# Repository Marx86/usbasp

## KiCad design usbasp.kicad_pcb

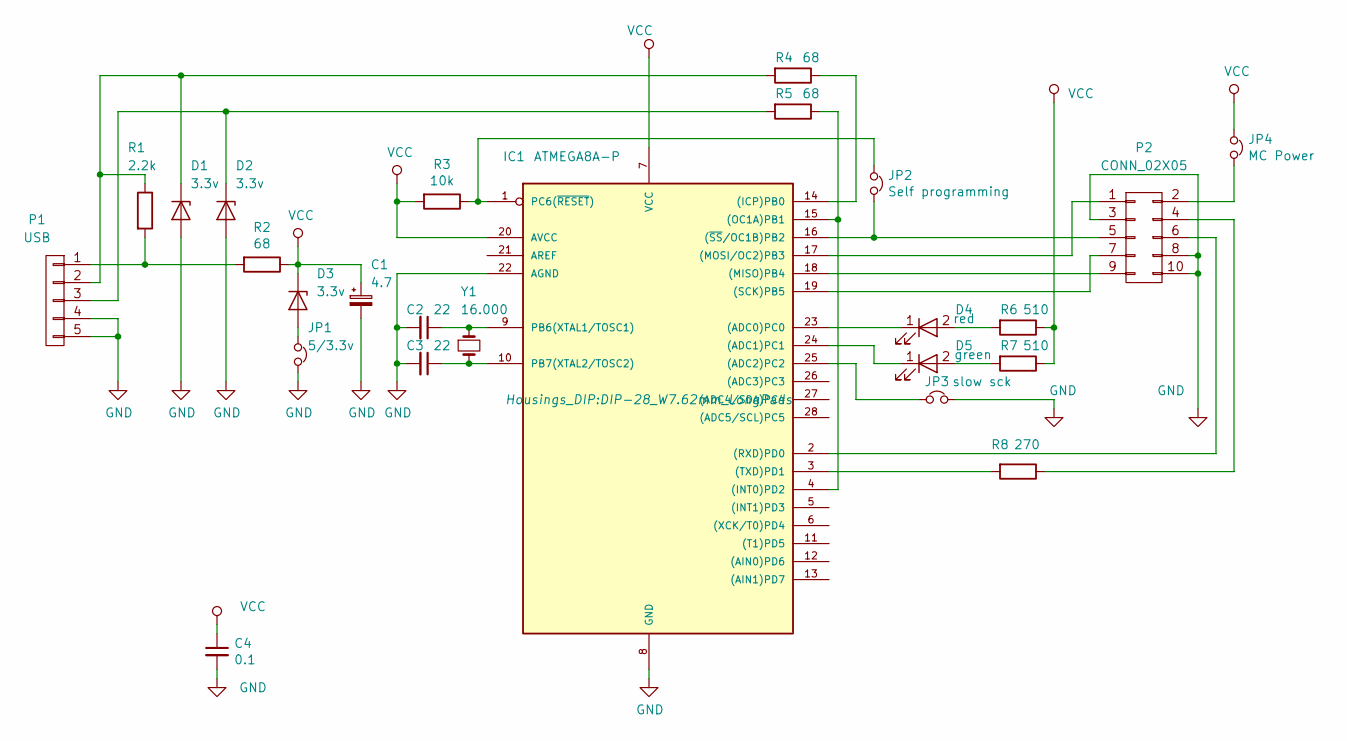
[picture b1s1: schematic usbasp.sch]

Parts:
C1: 4.7; CP_Radial_D5.0mm_P2.50mm
C2, C3: 22; C_1206
C4: 0.1; C_1206
D1, D2, D3: 3.3v; D_MiniMELF
D4: red; LED-3MM
D5: green; LED-3MM
IC1: ATMEGA8A-P; DIP-28_W7.62mm_LongPads
JP1: 5/3.3v; Pin_Header_Straight_1x02_Pitch2.54mm
JP2: Self programming; Pin_Header_Straight_1x02_Pitch2.54mm
JP3: slow sck; Pin_Header_Straight_1x02_Pitch2.54mm
JP4: MC Power; Pin_Header_Straight_1x02_Pitch2.54mm
P1: USB; USB_B
P2: CONN_02X05; Pin_Header_Straight_2x05_Pitch2.54mm
R1: 2.2k; R_1206
R2, R4, R5: 68; R_1206
R3: 10k; R_1206
R6, R7: 510; R_1206
R8: 270; R_1206
Y1: 16.000; Crystal_HC50-U_Vertical

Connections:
GND: C1.2, C2.2, C3.2, C4.2, D1.2 (A), D2.2 (A), IC1.8 (GND), IC1.22 (AGND), JP1.2, JP3.2, P1.4, P1.5, P2.3, P2.8, P2.10
unnamed: C2.1, IC1.9 (PB6(XTAL1/TOSC1)), Y1.1
unnamed: C3.1, IC1.10 (PB7(XTAL2/TOSC2)), Y1.2
unnamed: D1.1 (K), P1.2, R1.1, R4.2
unnamed: D2.1 (K), P1.3, R5.2
unnamed: D3.2 (A), JP1.1
unnamed: D4.1 (K), IC1.23 ((ADC0)PC0)
unnamed: D4.2 (A), R6.2
unnamed: D5.1 (K), IC1.24 ((ADC1)PC1)
unnamed: D5.2 (A), R7.2
unnamed: IC1.1 (PC6(~RESET~)), JP2.1, R3.1
unnamed: IC1.2 ((RXD)PD0), P2.6
unnamed: IC1.3 ((TXD)PD1), R8.2
unnamed: IC1.14 ((ICP)PB0), R4.1
unnamed: IC1.4 ((INT0)PD2), IC1.15 ((OC1A)PB1), R5.1
unnamed: IC1.16 ((~SS~/OC1B)PB2), JP2.2, P2.5
unnamed: IC1.17 ((MOSI/OC2)PB3), P2.1
unnamed: IC1.18 ((MISO)PB4), P2.9
unnamed: IC1.19 ((SCK)PB5), P2.7
unnamed: IC1.25 ((ADC2)PC2), JP3.1
unnamed: JP4.2, P2.2
unnamed: P1.1, R1.2, R2.2
unnamed: P2.4, R8.1
VCC: C1.1, C4.1, D3.1 (K), IC1.7 (VCC), IC1.20 (AVCC), JP4.1, R2.1, R3.2, R6.1, R7.1

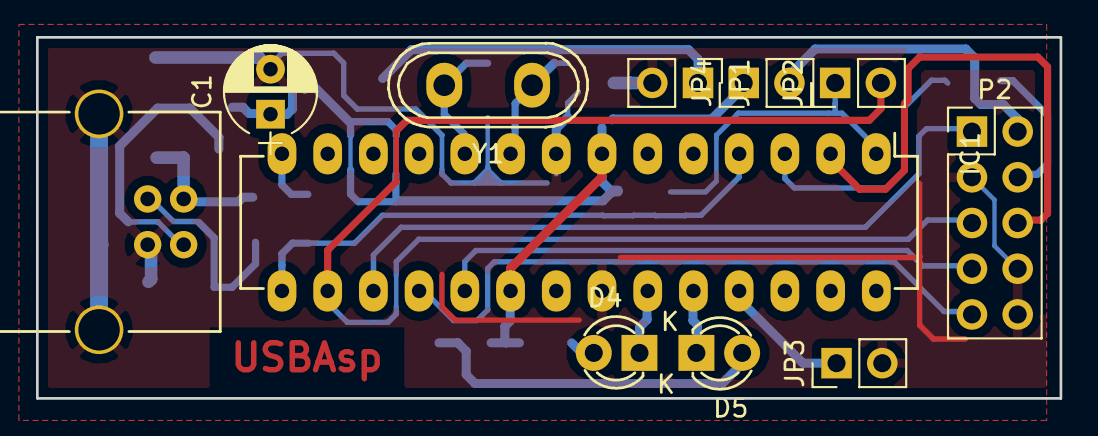
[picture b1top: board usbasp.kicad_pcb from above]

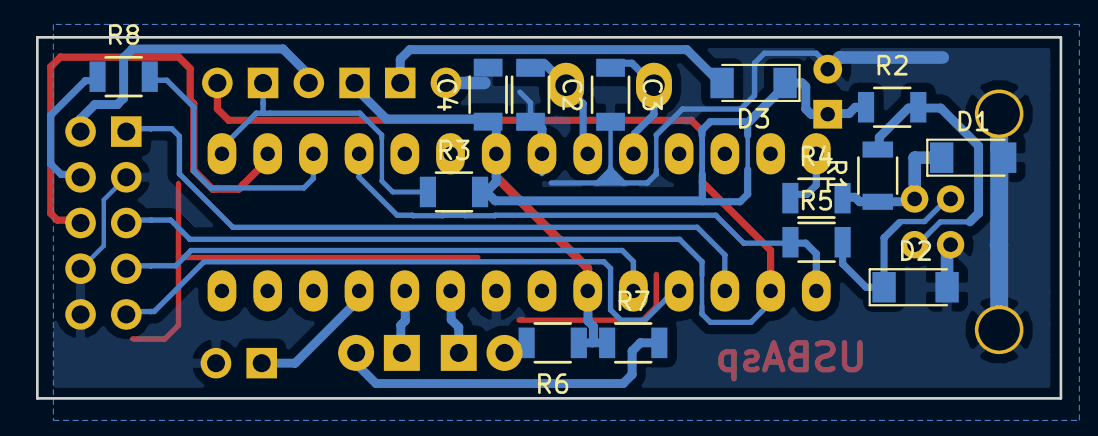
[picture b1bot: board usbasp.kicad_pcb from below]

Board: 2 copper layers, 56.9 x 20.1 mm, 25 parts (14 on the bottom side), 24 nets.

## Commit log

2016-12-16 Add Circuit and board
2018-02-08 Add source code and some PCB changes
2019-04-09 Update PCB
